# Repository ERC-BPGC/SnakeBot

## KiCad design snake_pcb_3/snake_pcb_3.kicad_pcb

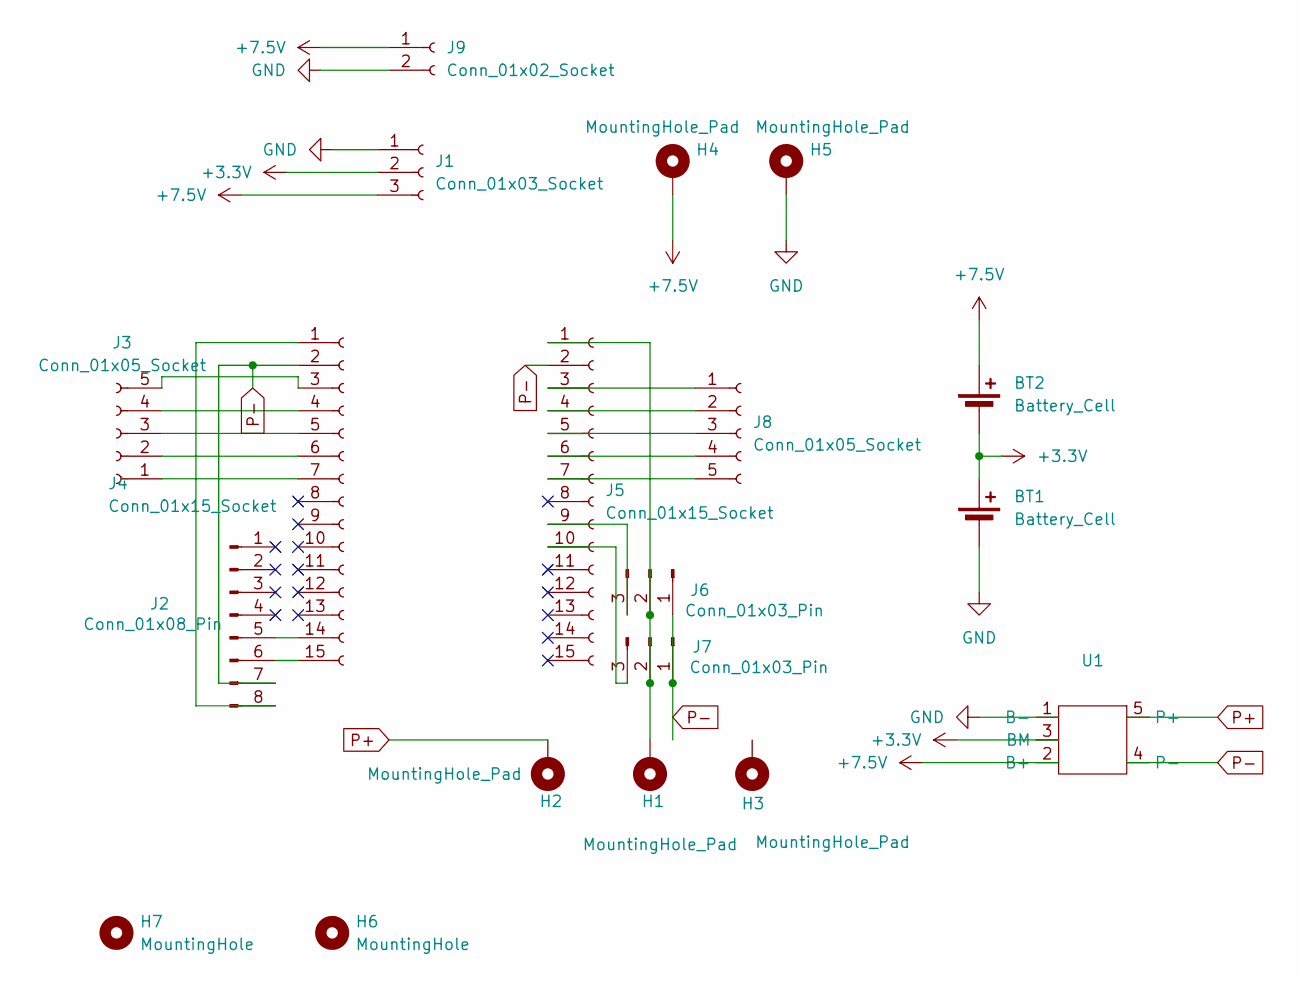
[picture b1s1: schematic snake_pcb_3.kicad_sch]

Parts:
BT1, BT2: Battery_Cell; BatteryHolder_Keystone_1042_1x18650
H1, H2, H3, H4, H5: MountingHole_Pad; MountingHole_2.2mm_M2_Pad
H6, H7: MountingHole; MountingHole_3.2mm_M3
J1: Conn_01x03_Socket; JST_XH_S3B-XH-A_1x03_P2.50mm_Horizontal
J2: Conn_01x08_Pin; PinHeader_1x08_P2.54mm_Vertical
J3, J8: Conn_01x05_Socket; PinSocket_1x05_P2.54mm_Vertical
J4, J5: Conn_01x15_Socket; PinSocket_1x15_P2.54mm_Vertical
J6, J7: Conn_01x03_Pin; PinHeader_1x03_P2.54mm_Vertical
J9: Conn_01x02_Socket; JST_XH_B2B-XH-AM_1x02_P2.50mm_Vertical
U1: hx-2s-01

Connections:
+3.3V: BT1.1 (+), BT2.2 (-), J1.2, U1.3 (BM)
+7.5V: BT2.1 (+), H4.1, J1.3, J9.1, U1.2 (B+)
GND: BT1.2 (-), H5.1, J1.1, J9.2, U1.1 (B-)
unnamed: J2.5, J4.14
unnamed: J2.6, J4.15
unnamed: J2.8, J4.1
unnamed: J3.1, J4.7
unnamed: J3.2, J4.6
unnamed: J3.3, J4.5
unnamed: J3.4, J4.4
unnamed: J3.5, J4.3
unnamed: H1.1, J5.1, J6.2, J7.2
unnamed: J5.3, J8.1
unnamed: J5.4, J8.2
unnamed: J5.5, J8.3
unnamed: J5.6, J8.4
unnamed: J5.7, J8.5
unnamed: J5.9, J6.3
unnamed: J5.10, J7.3
P+: H2.1, U1.5 (P+)
P-: J2.7, J4.2, J5.2, J6.1, J7.1, U1.4 (P-)

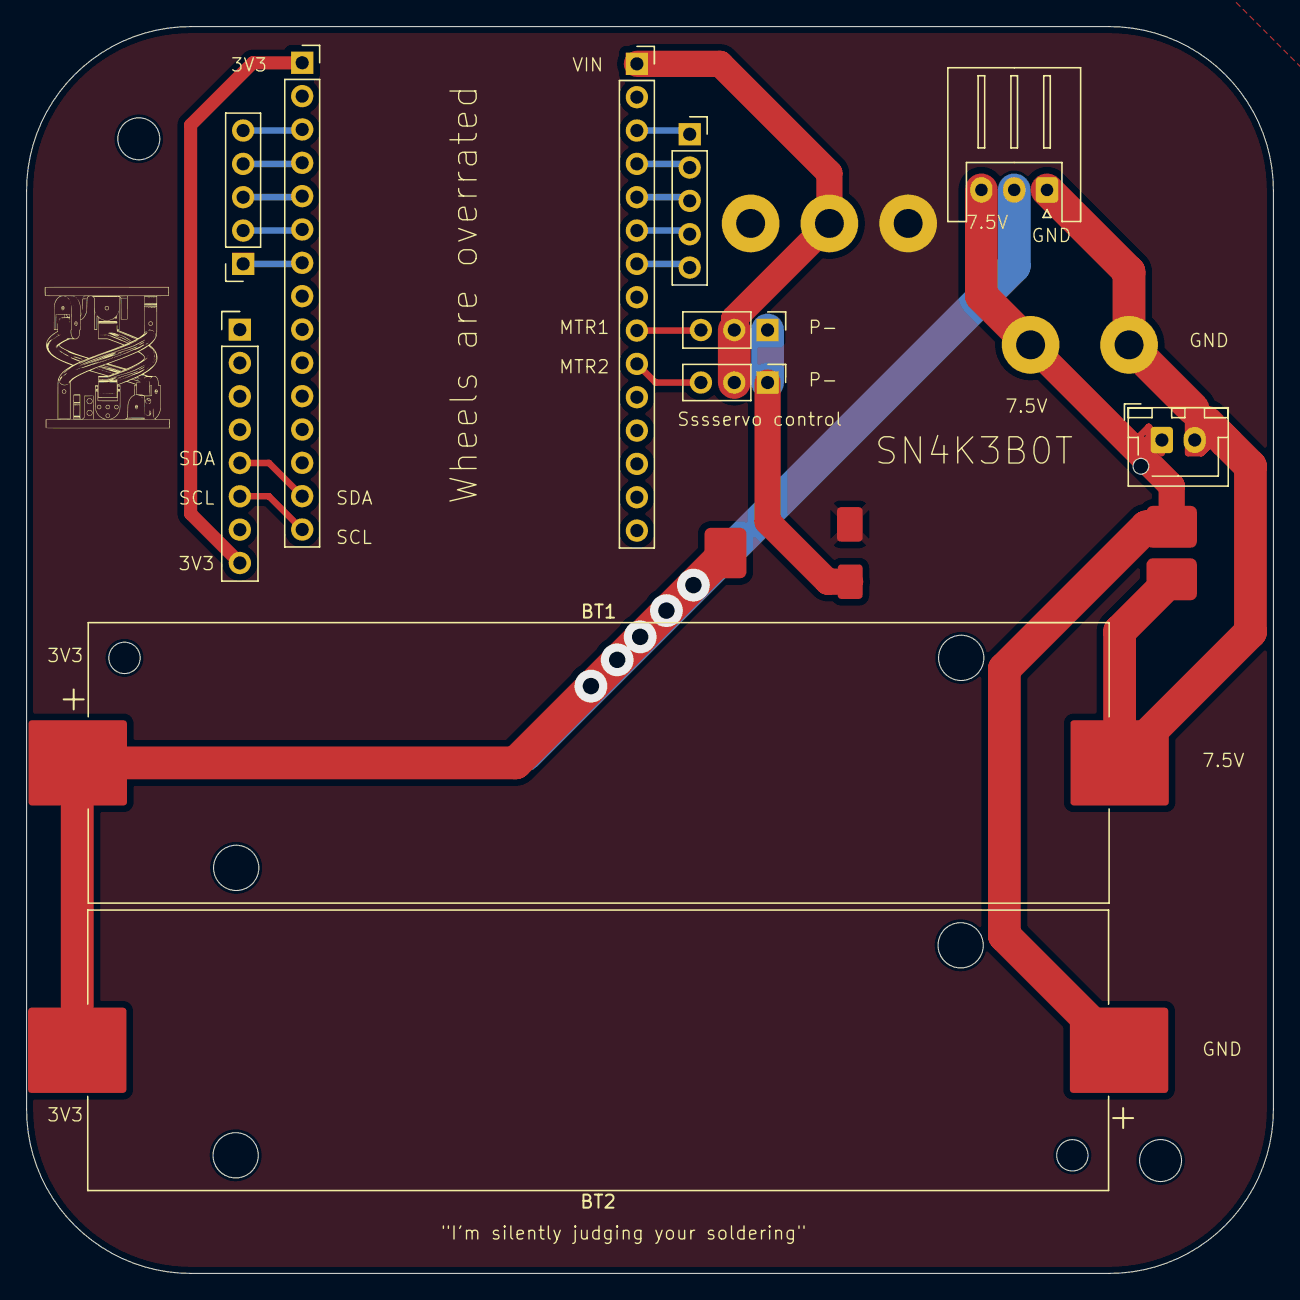
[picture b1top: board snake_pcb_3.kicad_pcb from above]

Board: 2 copper layers, 95.0 x 95.0 mm, 19 parts (0 on the bottom side), 21 nets.

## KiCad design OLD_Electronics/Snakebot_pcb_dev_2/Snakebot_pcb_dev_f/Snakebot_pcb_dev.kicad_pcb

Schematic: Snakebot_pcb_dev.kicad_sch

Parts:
C1, C8, C10: 22uF; C_0603_1608Metric_Pad1.08x0.95mm_HandSolder
C2, C6, C7, C9, C13, C14, C15: 0.1uF; C_0603_1608Metric_Pad1.08x0.95mm_HandSolder
C3, C11, C12: 1uF; C_0805_2012Metric_Pad1.18x1.45mm_HandSolder
C4, C5: 10uF; C_0805_2012Metric_Pad1.18x1.45mm_HandSolder
C16: 220pF; C_0603_1608Metric_Pad1.08x0.95mm_HandSolder
D1, D2, D3: LED; LED_0805_2012Metric_Pad1.15x1.40mm_HandSolder
H1, H2: MountingHole; MountingHole_3.2mm_M3
J1: Conn_01x04_Socket; JST_EH_S4B-EH_1x04_P2.50mm_Horizontal
J2, J5, J6: Conn_01x02_Socket; JST_EH_S2B-EH_1x02_P2.50mm_Horizontal
J3, J4: Conn_01x03_Socket; JST_EH_B3B-EH-A_1x03_P2.50mm_Vertical
J7, J8: Conn_01x08_Socket; JST_EH_B8B-EH-A_1x08_P2.50mm_Vertical
L1: 6.8uH; L_Bourns_SRN8040TA
R1, R6, R7: 10k; R_0603_1608Metric_Pad0.98x0.95mm_HandSolder
R2, R3, R4: 1K; R_0603_1608Metric_Pad0.98x0.95mm_HandSolder
R5: 50m; R_0603_1608Metric_Pad0.98x0.95mm_HandSolder
R8: 100k; R_0805_2012Metric_Pad1.20x1.40mm_HandSolder
R9, R10: 4.7k; R_0603_1608Metric_Pad0.98x0.95mm_HandSolder
SW1, SW2: SW_Push; SW_Push_1P1T_NO_CK_KSC6xxJ
SW3: SW_SPDT; SW_SPDT_CK_JS102011SAQN
U1: ESP32-WROOM-32E; ESP32-WROOM-32D
U2: AMS1117-3.3; SOT-223-3_TabPin2
U3: MP2615GQ-P; QFN-3x3_MP2615_MNP
U4: MPU-6050; InvenSense_QFN-24_4x4mm_P0.5mm

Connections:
+3.3V: C1.1, C2.1, C5.1, C13.2, C14.2, J7.7, J7.8, J8.1, R1.1, R9.1, R10.1, U1.2 (VDD), U2.2 (VO), U4.8 (VLOGIC), U4.13 (VDD)
+5V: J1.1, SW3.3 (C)
+7.5V: C10.1, J2.1, J3.2, J4.2, R5.2, SW3.1 (A), U3.9 (BATT)
BOOT: C7.1, J7.4, SW2.2, U1.25 (IO0)
EN: C3.2, C6.1, J7.3, J8.7, R1.2, SW1.2, U1.3 (EN)
GND: C1.2, C2.2, C3.1, C4.2, C5.2, C6.2, C7.2, C8.2, C10.2, C11.2, C12.1, C13.1, C14.1, C15.1, C16.2, D1.1 (K), J1.2, J2.2, J3.1, J4.1, J5.2, J6.2, J7.1, J7.2, J8.8, R7.2, R8.1, SW1.1, SW2.1, U1.1 (GND), U1.15 (GND), U1.38 (GND), U1.39 (GND), U2.1 (GND), U3.4 (CELL), U3.5 (SEL), U3.8 (AGND), U3.16 (PGND), U4.1 (CLKIN), U4.9 (AD0), U4.11 (FSYNC), U4.18 (GND)
IO25: J8.4, U1.10 (IO25)
IO26: J8.3, U1.11 (IO26)
IO27: J8.2, U1.12 (IO27)
IO32: J8.6, U1.8 (IO32)
IO33: J8.5, U1.9 (IO33)
MOTOR_H: J3.3, U1.27 (IO16)
MOTOR_V: J4.3, U1.28 (IO17)
unnamed: D1.2 (A), R2.2
unnamed: D2.2 (A), R3.2
unnamed: D2.1 (K), U3.12 (*ACOK)
unnamed: D3.2 (A), R4.2
unnamed: D3.1 (K), U3.11 (*CHGOK)
unnamed: C4.1, R2.1, SW3.2 (B), U2.3 (VI)
unnamed: R8.2, U3.6 (*EN)
unnamed: C9.1, L1.1, U3.15 (BST)
unnamed: L1.2, R5.1, U3.10 (CSP)
unnamed: R6.2, R7.1, U3.13 (NTC)
unnamed: C9.2, U3.1 (SW)
unnamed: C11.1, U3.14 (TMR)
unnamed: C12.2, R6.1, U3.3 (VCC)
unnamed: C16.1, U4.20 (CPOUT)
unnamed: C15.2, U4.10 (REGOUT)
RX: J1.4, U1.34 (RXD0/IO3)
RX2: J7.5, U1.31 (IO19)
SCL: R9.2, U1.36 (IO22), U4.23 (SCL)
SDA: R10.2, U1.33 (IO21), U4.24 (SDA)
TX: J1.3, U1.35 (TXD0/IO1)
TX2: J7.6, U1.30 (IO18)
VCC: C8.1, J5.1, J6.1, R3.1, R4.1, U3.2 (VIN)

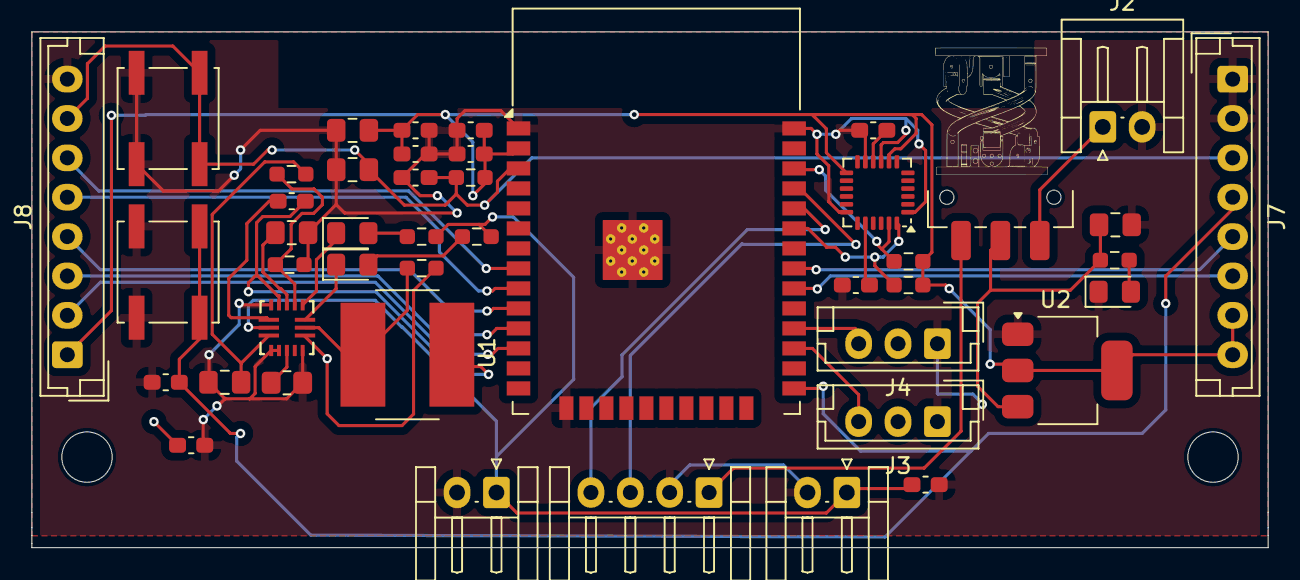
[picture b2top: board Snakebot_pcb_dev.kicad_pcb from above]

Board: 2 copper layers, 78.5 x 32.8 mm, 47 parts (0 on the bottom side), 35 nets.

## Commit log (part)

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2024-08-15 Add files via upload
    "fsolve is a local solver that doesn't always guarantee the solution satisfies all constraints, especially when dealing with complex systems of equations and starting points that may lead to a soluti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
2024-08-17 Add files via upload
    cleaned up code and added comments
2024-08-22 Add files via upload
    added animating and fixed issue with real angles
2024-08-27 Add files via upload
    Added the PCB schematic as done so far.
2024-08-27 Add files via upload
    minor changes to schematic including establishing connections between rp2040 and memory. Also added ground and voltage in other places
2024-09-07 launch file
2024-09-23 Restructuring Repository
2024-10-05 Add files via upload
    PCB schematic done, layout in progress.
2024-10-24 Update figure_out_snake_v6.2.py
    slight change in angles calculated
2024-11-19 Add files via upload
    Arduino code that takes angle from serial monitor and turn servos accordingly.
2024-11-19 Create file1
2024-11-19 Rename Controls/Snake.ino to Controls/Arduino Controller/Snake.ino
2024-11-19 Add files via upload
    To get the initial position of all servos to default at 90 degrees
2024-11-22 Update Snake.ino
    Last iterations had a few bugs
2024-11-22 Update Snake.ino
    To accommodate the inverted motors
2024-11-22 Update Snake.ino
    Constrained the angles to 70 and 110
2025-01-16 Add files via upload
    New method to find angles, doesnt use any SciPy functions, decreasing the accuracy a little, but making it faster and more reliable
2025-01-21 Add files via upload
    simplified version of v7, designed specifcally to get the angles for basic urdf simulations
2025-02-25 Add files via upload
    Arduino code that iteratively serially receives and sets servo angles
2025-02-25 Add files via upload
    will modify it a bit more, but this one is working near perfectly with the AngleReceivingCode.ino
2025-04-03 Initial commit - uploading snake_robot_harmonic_ws
2025-05-14 Deleted unnecessary folders
2025-05-14 Snake simulation V2
2025-05-14 Remove submodule snake_robot_harmonic_ws
2025-05-14 Removed .git directory from mujoco_playground_unitree
2025-05-15 Gymnasium update
2025-05-15 requirements.txt added
2025-05-15 added examples gifs
2025-05-15 added gymnasium set ups -no RL
2025-08-27 Reorganize project structure and fix MJCF relative path
2025-12-29 Adding new electronics and mech + restructuring
2026-01-07 Adding new esp code
2026-01-13 added meshes
2026-02-28 new merged auto scripts
2026-03-02 converted path followed to phase shifting code , to figure out properly
